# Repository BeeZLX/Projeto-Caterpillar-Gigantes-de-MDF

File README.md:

Programação de HardWare 2025

Grupo Caterpillar:

Vinicius Regis
Leticia Ribeiro
Caio Rodrigues

O projeto Gigantes de MDF envolve a criação integral de um robô móvel construído em MDF, incluindo todo o sistema de locomoção formado por motores DC acionados por PWM, um mecanismo de disparo a laser utilizando um diodo emissor de luz vermelho e um módulo de detecção baseado em LDR acoplado a um difusor.

A proposta do trabalho é colocar em prática os conteúdos estudados na disciplina de Programação de Hardware, operando diretamente com o microcontrolador ATmega328p, buscando apenas pelos componentes essenciais para o funcionamento básico do sistema.

Regras do Edital:
Dimensões máximas de 200 × 200 × 200 mm • Sistema com 2 a 4 rodas, capaz de realizar movimentação no próprio eixo • “Arma” laser posicionada no centro do robô, a 100 mm de altura • Receptor de luz instalado ao lado direito da arma, com difusor de 20 mm • Estrutura baseada em MDF, com cortes e montagem conforme projeto disponibilizado

O gigante de MDF deve cumprir as seguintes especificações:
 Utilizar o Microcontrolador ATmega328P, ter Controle dos motores via PWM, Laser temporizado por Timer, Receptor de luz (LDR) com rotina de interrupção, após cada acerto é obrigatorio ter um delay, utilização de leds para a simulação da "vida" do robõ, Rotina de giro automático de 180°, Reset de vidas via interrupção externa e ter o Código completamente documentado em Doxygen

Todo o conjunto — circuito eletrônico, firmware e documentação — foi idealizado, desenvolvido e implementado pela equipe.

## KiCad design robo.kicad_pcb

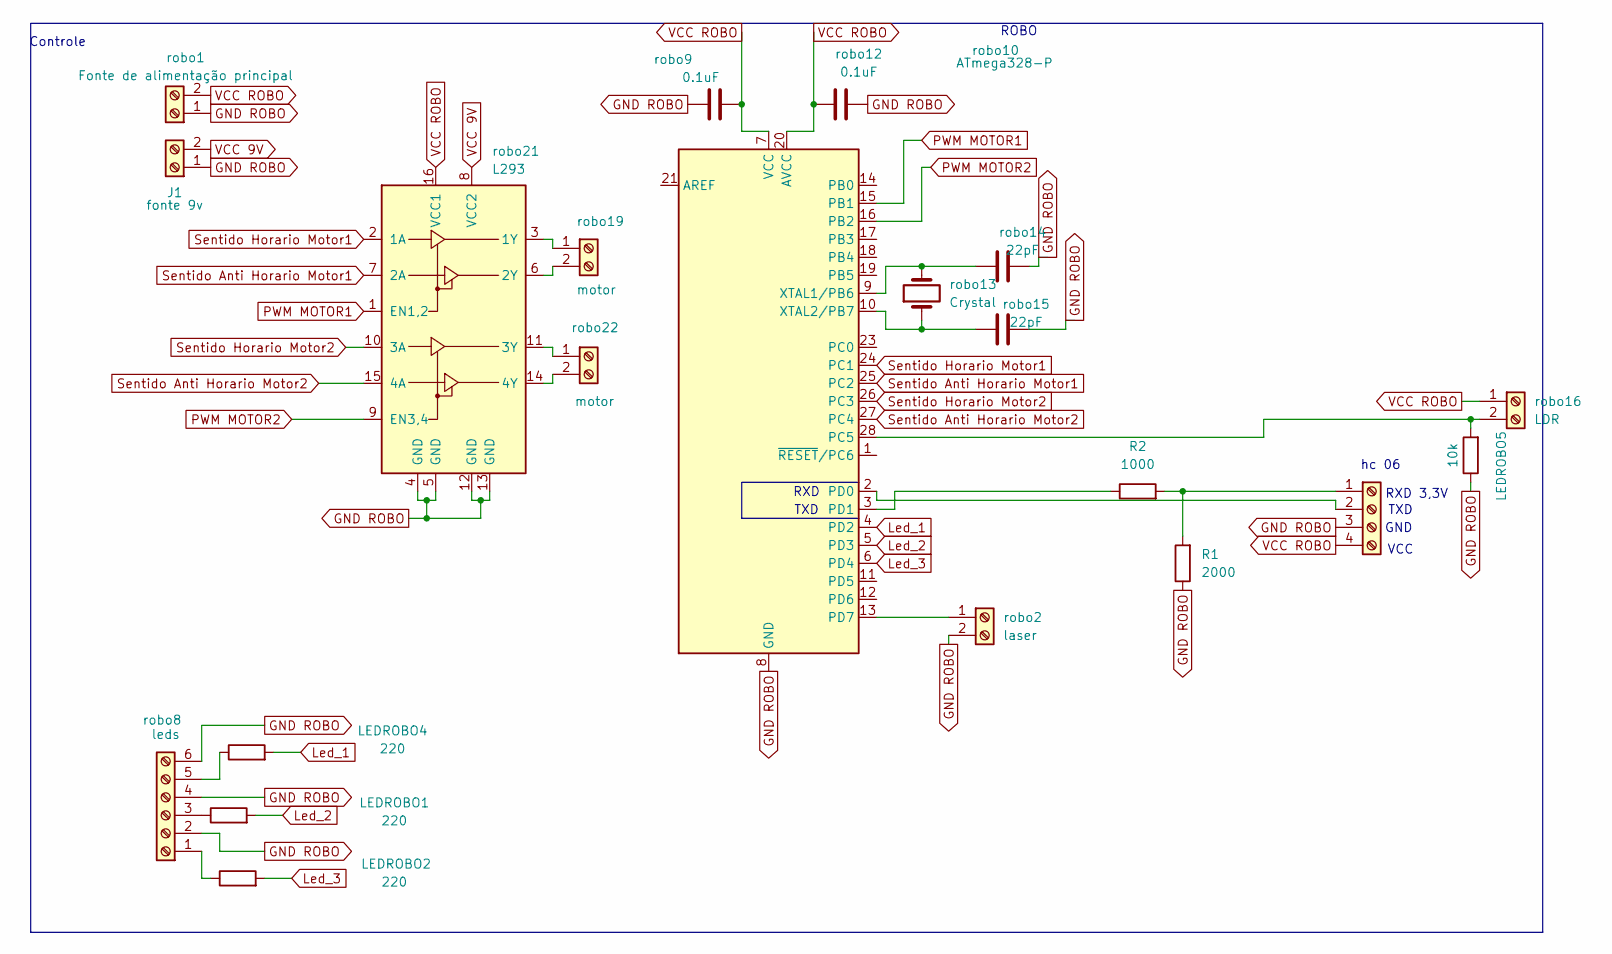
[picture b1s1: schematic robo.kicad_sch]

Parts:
J1: fonte 9v; TerminalBlock_CUI_TB007-508-02_1x02_P5.08mm_Horizontal
J3: hc06; TerminalBlock_CUI_TB007-508-04_1x04_P5.08mm_Horizontal
LEDROBO1, LEDROBO2, LEDROBO4: 220; R_Axial_DIN0309_L9.0mm_D3.2mm_P15.24mm_Horizontal
LEDROBO5: 10k; R_Axial_DIN0309_L9.0mm_D3.2mm_P15.24mm_Horizontal
R1: 2000; R_Axial_DIN0309_L9.0mm_D3.2mm_P15.24mm_Horizontal
R2: 1000; R_Axial_DIN0309_L9.0mm_D3.2mm_P15.24mm_Horizontal
robo1: Fonte de alimentação principal; TerminalBlock_CUI_TB007-508-02_1x02_P5.08mm_Horizontal
robo2: laser; TerminalBlock_CUI_TB007-508-02_1x02_P5.08mm_Horizontal
robo8: leds; TerminalBlock_CUI_TB007-508-06_1x06_P5.08mm_Horizontal
robo9, robo12: 0.1uF; CP_Radial_D7.5mm_P2.50mm
robo10: ATmega328-P; DIP-28_W7.62mm
robo13: Crystal; Crystal_HC49-4H_Vertical
robo14, robo15: 22pF; CP_Radial_D7.5mm_P2.50mm
robo16: LDR; TerminalBlock_CUI_TB007-508-02_1x02_P5.08mm_Horizontal
robo19, robo22: motor; TerminalBlock_CUI_TB007-508-02_1x02_P5.08mm_Horizontal
robo21: L293; DIP-16_W7.62mm

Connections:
GND ROBO: J1.1, J3.3, LEDROBO5.1, R1.1, robo1.1, robo2.2, robo8.2, robo8.4, robo8.6, robo9.1, robo10.8 (GND), robo10.22 (GND), robo12.1, robo14.2, robo15.2, robo21.4 (GND), robo21.5 (GND), robo21.12 (GND), robo21.13 (GND)
Led_1: LEDROBO4.2, robo10.4 (PD2)
Led_2: LEDROBO1.2, robo10.5 (PD3)
Led_3: LEDROBO2.2, robo10.6 (PD4)
unnamed: J3.1, R1.2, R2.2
unnamed: J3.2, robo10.2 (PD0)
unnamed: LEDROBO2.1, robo8.1
unnamed: LEDROBO1.1, robo8.3
unnamed: LEDROBO4.1, robo8.5
unnamed: LEDROBO5.2, robo10.28 (PC5), robo16.2
unnamed: R2.1, robo10.3 (PD1)
unnamed: robo2.1, robo10.13 (PD7)
unnamed: robo10.9 (XTAL1/PB6), robo13.2, robo14.1
unnamed: robo10.10 (XTAL2/PB7), robo13.1, robo15.1
unnamed: robo19.1, robo21.3 (1Y)
unnamed: robo19.2, robo21.6 (2Y)
unnamed: robo21.11 (3Y), robo22.1
unnamed: robo21.14 (4Y), robo22.2
PWM MOTOR1: robo10.15 (PB1), robo21.1 (EN1,2)
PWM MOTOR2: robo10.16 (PB2), robo21.9 (EN3,4)
Sentido Anti Horario Motor1: robo10.25 (PC2), robo21.7 (2A)
Sentido Anti Horario Motor2: robo10.27 (PC4), robo21.15 (4A)
Sentido Horario Motor1: robo10.24 (PC1), robo21.2 (1A)
Sentido Horario Motor2: robo10.26 (PC3), robo21.10 (3A)
VCC 9V: J1.2, robo21.8 (VCC2)
VCC ROBO: J3.4, robo1.2, robo9.2, robo10.7 (VCC), robo10.20 (AVCC), robo12.2, robo16.1, robo21.16 (VCC1)

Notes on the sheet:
ROBO
RXD 3,3V
GND
Controle
TXD
VCC
RXD
hc 06

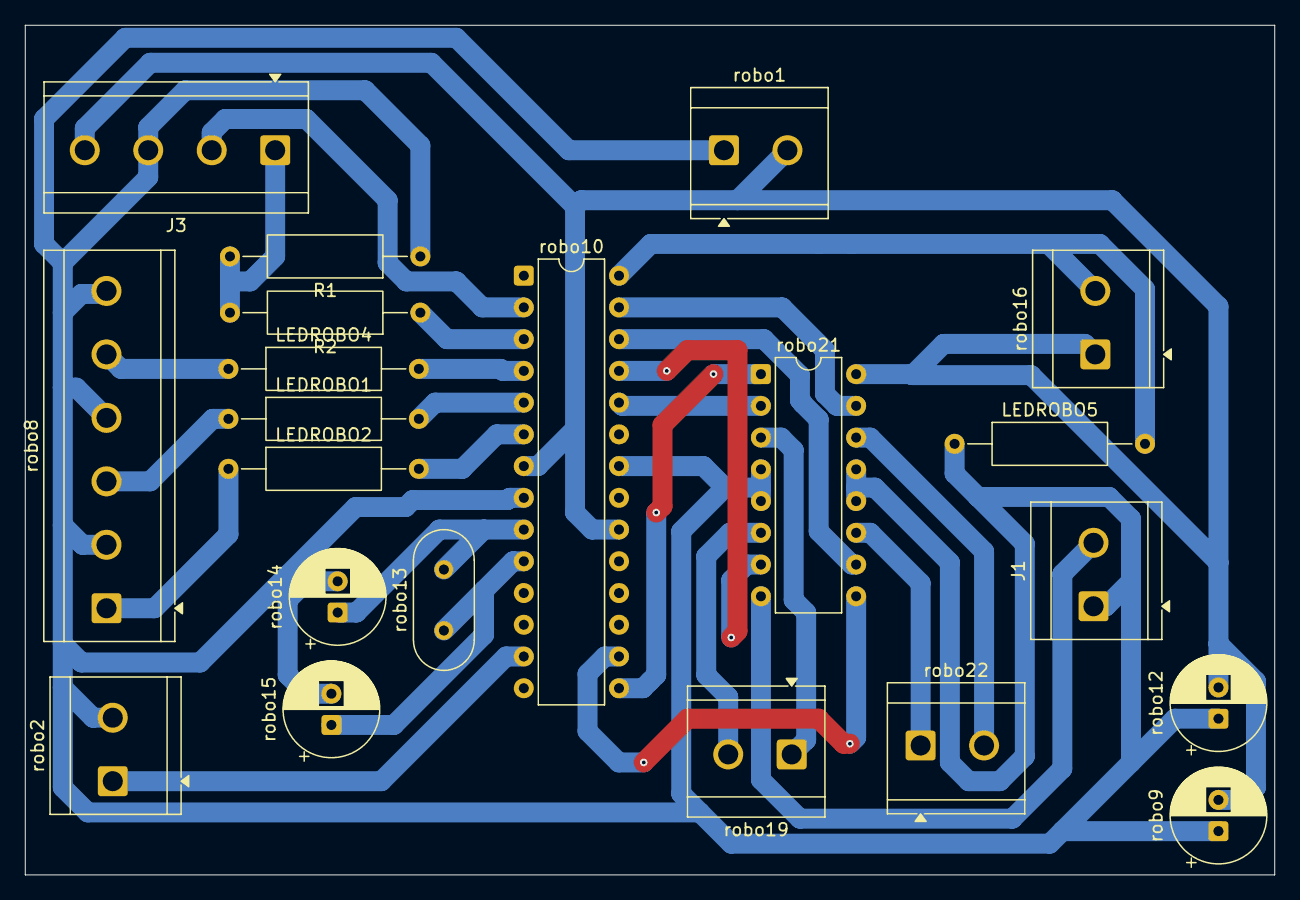
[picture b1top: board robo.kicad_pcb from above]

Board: 2 copper layers, 100.0 x 68.0 mm, 21 parts (0 on the bottom side), 26 nets.

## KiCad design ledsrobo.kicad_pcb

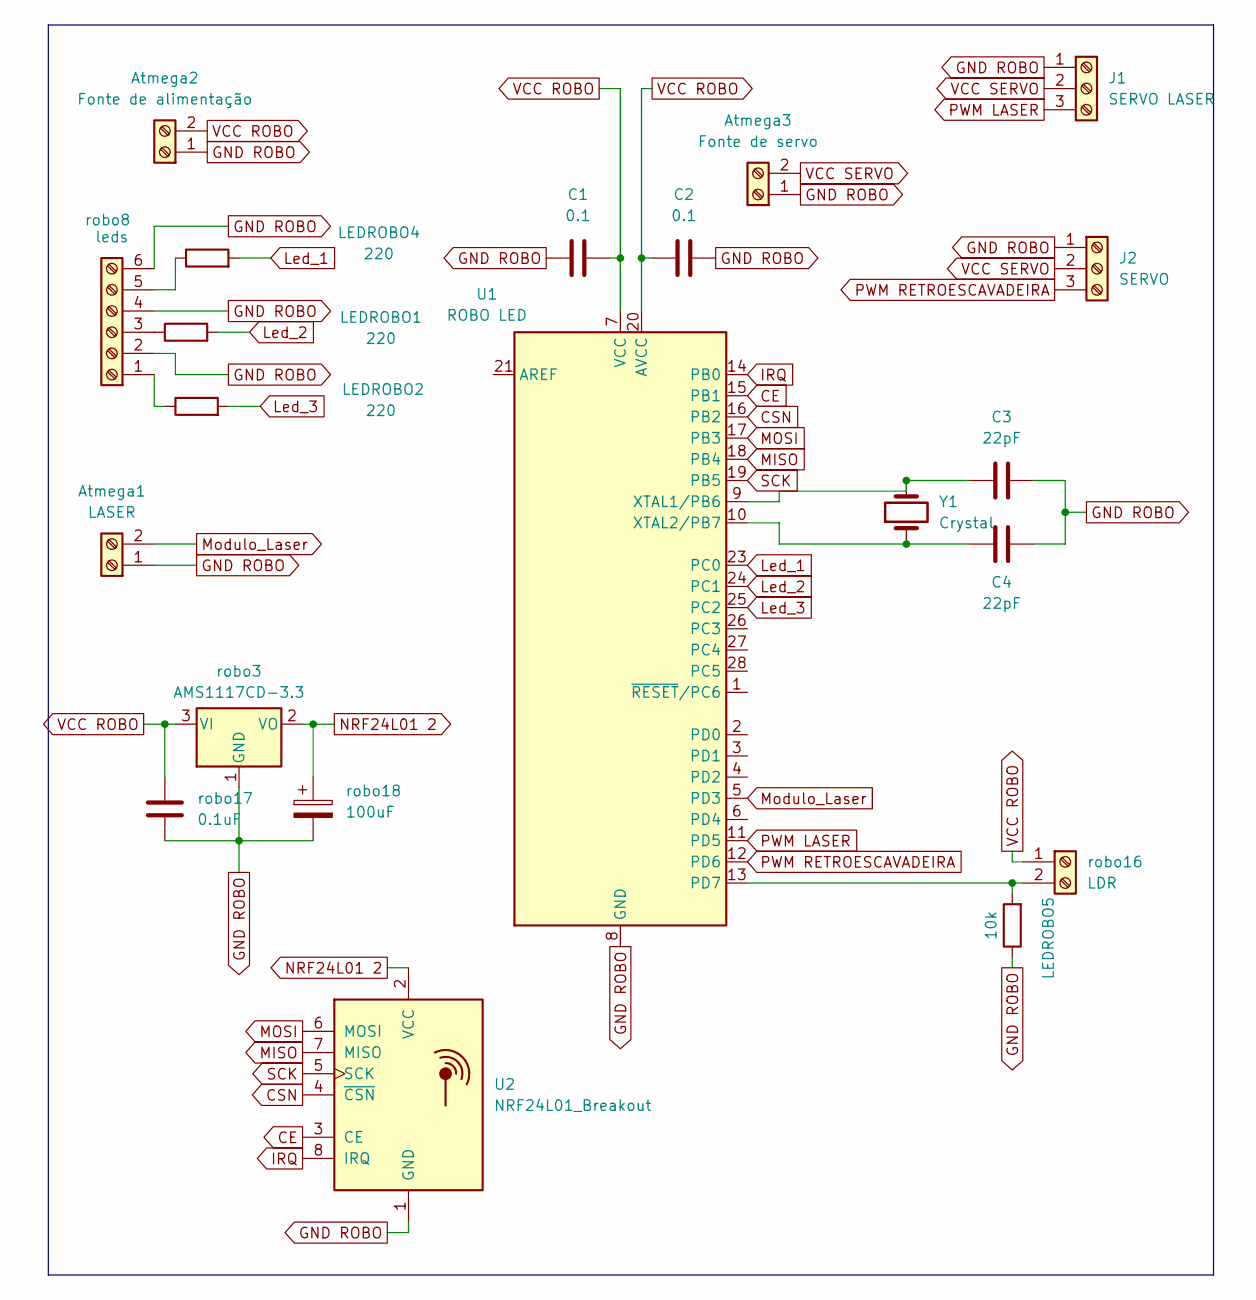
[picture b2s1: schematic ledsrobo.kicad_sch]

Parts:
Atmega1: LASER; TerminalBlock_CUI_TB007-508-02_1x02_P5.08mm_Horizontal
Atmega2: Fonte de alimentação; TerminalBlock_CUI_TB007-508-02_1x02_P5.08mm_Horizontal
Atmega3: Fonte de servo; TerminalBlock_CUI_TB007-508-02_1x02_P5.08mm_Horizontal
C1, C2: 0.1; CP_Radial_D7.5mm_P2.50mm
C3, C4: 22pF; CP_Radial_D7.5mm_P2.50mm
J1: SERVO LASER; TerminalBlock_CUI_TB007-508-03_1x03_P5.08mm_Horizontal
J2: SERVO; TerminalBlock_CUI_TB007-508-03_1x03_P5.08mm_Horizontal
LEDROBO1, LEDROBO2, LEDROBO4: 220; R_Axial_DIN0309_L9.0mm_D3.2mm_P15.24mm_Horizontal
LEDROBO5: 10k; R_Axial_DIN0309_L9.0mm_D3.2mm_P15.24mm_Horizontal
U1: ROBO LED; DIP-28_W7.62mm
U2: NRF24L01_Breakout; nRF24L01_Breakout
Y1: Crystal; Crystal_HC49-4H_Vertical
robo3: AMS1117CD-3.3; TerminalBlock_CUI_TB007-508-03_1x03_P5.08mm_Horizontal
robo8: leds; TerminalBlock_CUI_TB007-508-06_1x06_P5.08mm_Horizontal
robo16: LDR; TerminalBlock_CUI_TB007-508-02_1x02_P5.08mm_Horizontal
robo17: 0.1uF; CP_Radial_D7.5mm_P2.50mm
robo18: 100uF; CP_Radial_D7.5mm_P2.50mm

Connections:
CE: U1.15 (PB1), U2.3 (CE)
CSN: U1.16 (PB2), U2.4 (~CSN)
GND ROBO: Atmega1.1, Atmega2.1, Atmega3.1, C1.2, C2.1, C3.1, C4.1, J1.1, J2.1, LEDROBO5.1, U1.8 (GND), U1.22 (GND), U2.1 (GND), robo3.1 (GND), robo8.2, robo8.4, robo8.6, robo17.1, robo18.2
IRQ: U1.14 (PB0), U2.8 (IRQ)
Led_1: LEDROBO4.2, U1.23 (PC0)
Led_2: LEDROBO1.2, U1.24 (PC1)
Led_3: LEDROBO2.2, U1.25 (PC2)
MISO: U1.18 (PB4), U2.7 (MISO)
MOSI: U1.17 (PB3), U2.6 (MOSI)
Modulo_Laser: Atmega1.2, U1.5 (PD3)
NRF24L01 2: U2.2 (VCC), robo3.2 (VO), robo18.1
unnamed 11: LEDROBO5.2, U1.13 (PD7), robo16.2; also elsewhere on the board
unnamed: C3.2, U1.9 (XTAL1/PB6), Y1.2
unnamed: C4.2, U1.10 (XTAL2/PB7), Y1.1
unnamed: LEDROBO2.1, robo8.1
unnamed: LEDROBO1.1, robo8.3
unnamed: LEDROBO4.1, robo8.5
PWM LASER: J1.3, U1.11 (PD5)
PWM RETROESCAVADEIRA: J2.3, U1.12 (PD6)
SCK: U1.19 (PB5), U2.5 (SCK)
VCC ROBO: Atmega2.2, C1.1, C2.2, U1.7 (VCC), U1.20 (AVCC), robo3.3 (VI), robo16.1, robo17.2
VCC SERVO: Atmega3.2, J1.2, J2.2

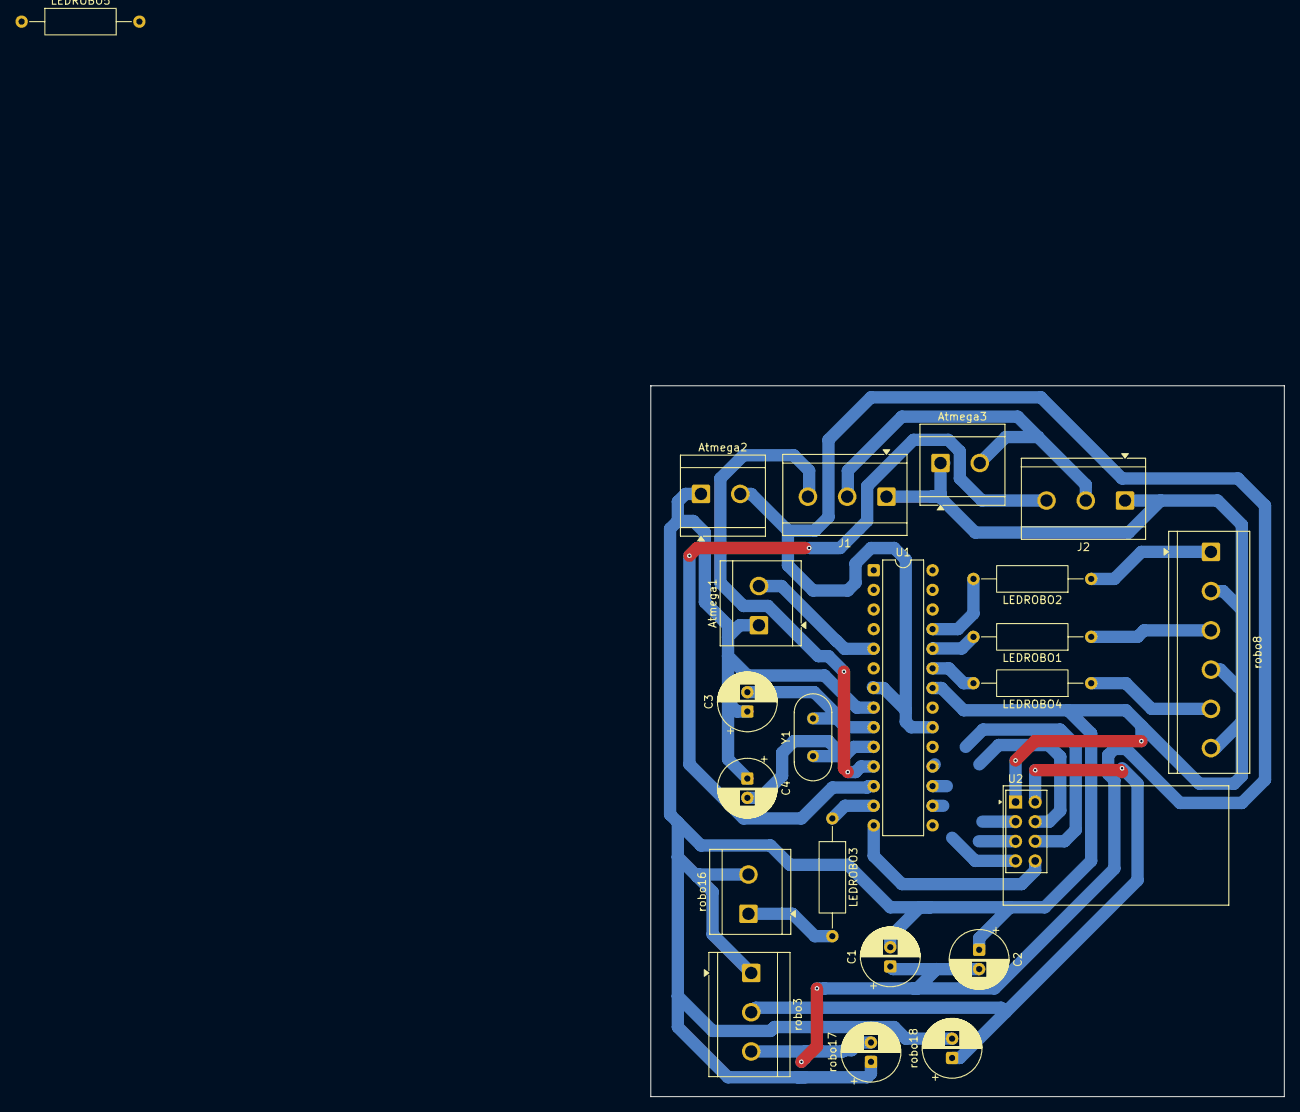
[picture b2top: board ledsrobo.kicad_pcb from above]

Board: 2 copper layers, 82.0 x 92.0 mm, 22 parts (0 on the bottom side), 22 nets.

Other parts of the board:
LEDROBO3: 10k; R_Axial_DIN0309_L9.0mm_D3.2mm_P15.24mm_Horizontal

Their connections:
unnamed 11: LEDROBO3.1; also elsewhere on the board

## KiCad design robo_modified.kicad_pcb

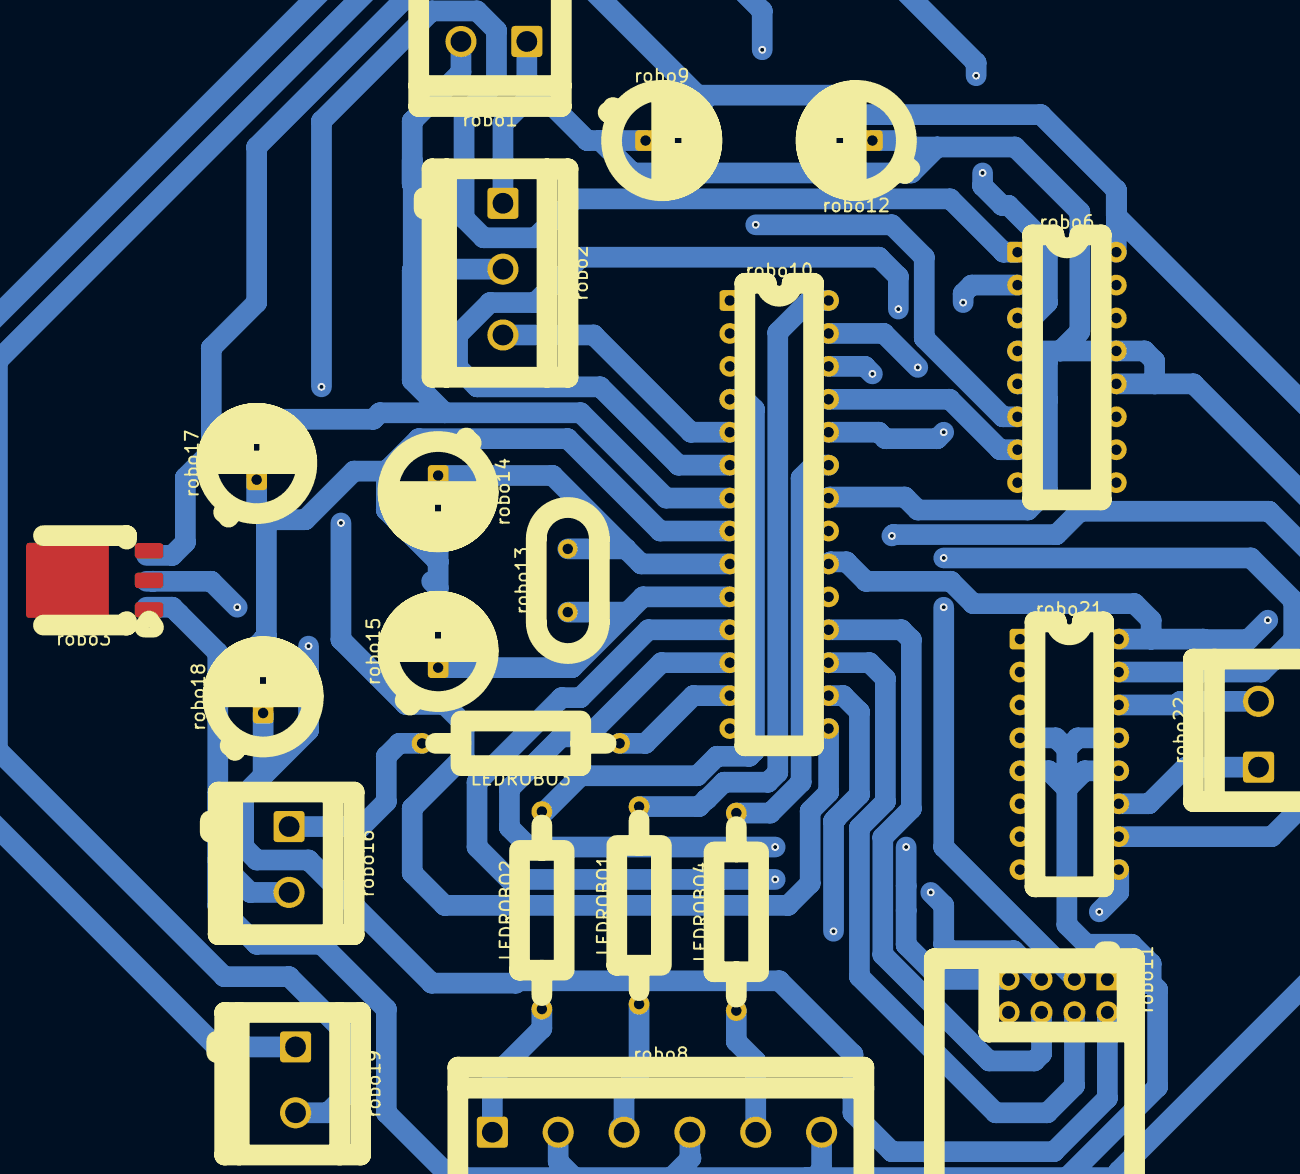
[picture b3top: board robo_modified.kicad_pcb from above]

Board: 2 copper layers, 22 parts (0 on the bottom side), 29 nets.

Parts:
LEDROBO1, LEDROBO2, LEDROBO4: 220; R_Axial_DIN0309_L9.0mm_D3.2mm_P15.24mm_Horizontal
LEDROBO3: 10k; R_Axial_DIN0309_L9.0mm_D3.2mm_P15.24mm_Horizontal
robo1: Fonte de alimentação principal; TerminalBlock_CUI_TB007-508-02_1x02_P5.08mm_Horizontal
robo2: Laser; TerminalBlock_CUI_TB007-508-03_1x03_P5.08mm_Horizontal
robo3: AMS1117CD-3.3; TO-252-3_TabPin2
robo6, robo21: L293; DIP-16_W7.62mm
robo8: leds; TerminalBlock_CUI_TB007-508-06_1x06_P5.08mm_Horizontal
robo9, robo12, robo17: 0.1uF; CP_Radial_D7.5mm_P2.50mm
robo10: ATmega328-P; DIP-28_W7.62mm
robo11: NRF24L01_Breakout; nRF24L01_Breakout
robo13: Crystal; Crystal_HC49-4H_Vertical
robo14, robo15: C; CP_Radial_D7.5mm_P2.50mm
robo16: LDR; TerminalBlock_CUI_TB007-508-02_1x02_P5.08mm_Horizontal
robo18: 100uF; CP_Radial_D7.5mm_P2.50mm
robo19, robo22: motor; TerminalBlock_CUI_TB007-508-02_1x02_P5.08mm_Horizontal

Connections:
Digital NRF03 2: robo10.6 (PD4), robo11.3 (CE)
Digital NRF05 2: robo10.11 (PD5), robo11.5 (SCK)
Digital NRF07 2: robo10.12 (PD6), robo11.7 (MISO)
GND ROBO: robo1.1, robo2.1, robo3.1 (GND), robo6.4 (GND), robo6.5 (GND), robo6.12 (GND), robo6.13 (GND), robo8.2, robo8.4, robo8.6, robo9.1, robo10.8 (GND), robo10.22 (GND), robo11.1 (GND), robo12.1, robo14.2, robo15.2, robo16.2, robo17.1, robo18.2, robo21.4 (GND), robo21.5 (GND), robo21.12 (GND), robo21.13 (GND)
Led_1: LEDROBO4.2, robo10.23 (PC0)
Led_2: LEDROBO1.2, robo10.28 (PC5)
Led_3: LEDROBO2.2, robo10.4 (PD2)
Modulo_Laser: robo2.3, robo10.5 (PD3)
NRF24L01 2: robo3.2 (VO), robo11.2 (VCC), robo18.1
unnamed: LEDROBO2.1, robo8.1
unnamed: LEDROBO1.1, robo8.3
unnamed: LEDROBO4.1, robo8.5
unnamed: LEDROBO3.1, robo10.13 (PD7)
unnamed: robo10.9 (XTAL1/PB6), robo13.2, robo14.1
unnamed: robo10.10 (XTAL2/PB7), robo13.1, robo15.1
unnamed: LEDROBO3.2, robo16.1
unnamed: robo6.3 (1Y), robo19.1
unnamed: robo6.6 (2Y), robo19.2
unnamed: robo21.11 (3Y), robo22.1
unnamed: robo21.14 (4Y), robo22.2
PWM MOTOR1: robo6.1 (EN1,2), robo10.15 (PB1)
PWM MOTOR2: robo10.16 (PB2), robo21.9 (EN3,4)
PWM NRF04 2: robo10.17 (PB3), robo11.4 (~CSN)
PWM NRF06 2: robo10.18 (PB4), robo11.6 (MOSI)
Sentido Anti Horario Motor1: robo6.7 (2A), robo10.25 (PC2)
Sentido Anti Horario Motor2: robo10.27 (PC4), robo21.15 (4A)
Sentido Horario Motor1: robo6.2 (1A), robo10.24 (PC1)
Sentido Horario Motor2: robo10.26 (PC3), robo21.10 (3A)
VCC ROBO: robo1.2, robo2.2, robo3.3 (VI), robo6.16 (VCC1), robo9.2, robo10.7 (VCC), robo10.20 (AVCC), robo12.2, robo17.2, robo21.16 (VCC1)

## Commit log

2025-11-29 Documentação Word
2025-11-29 Simulide
2025-11-29 Placa 2 (Arma) (Servos Motor)
2025-11-29 Placa 1 (Coração)
2025-11-29 Read.me
